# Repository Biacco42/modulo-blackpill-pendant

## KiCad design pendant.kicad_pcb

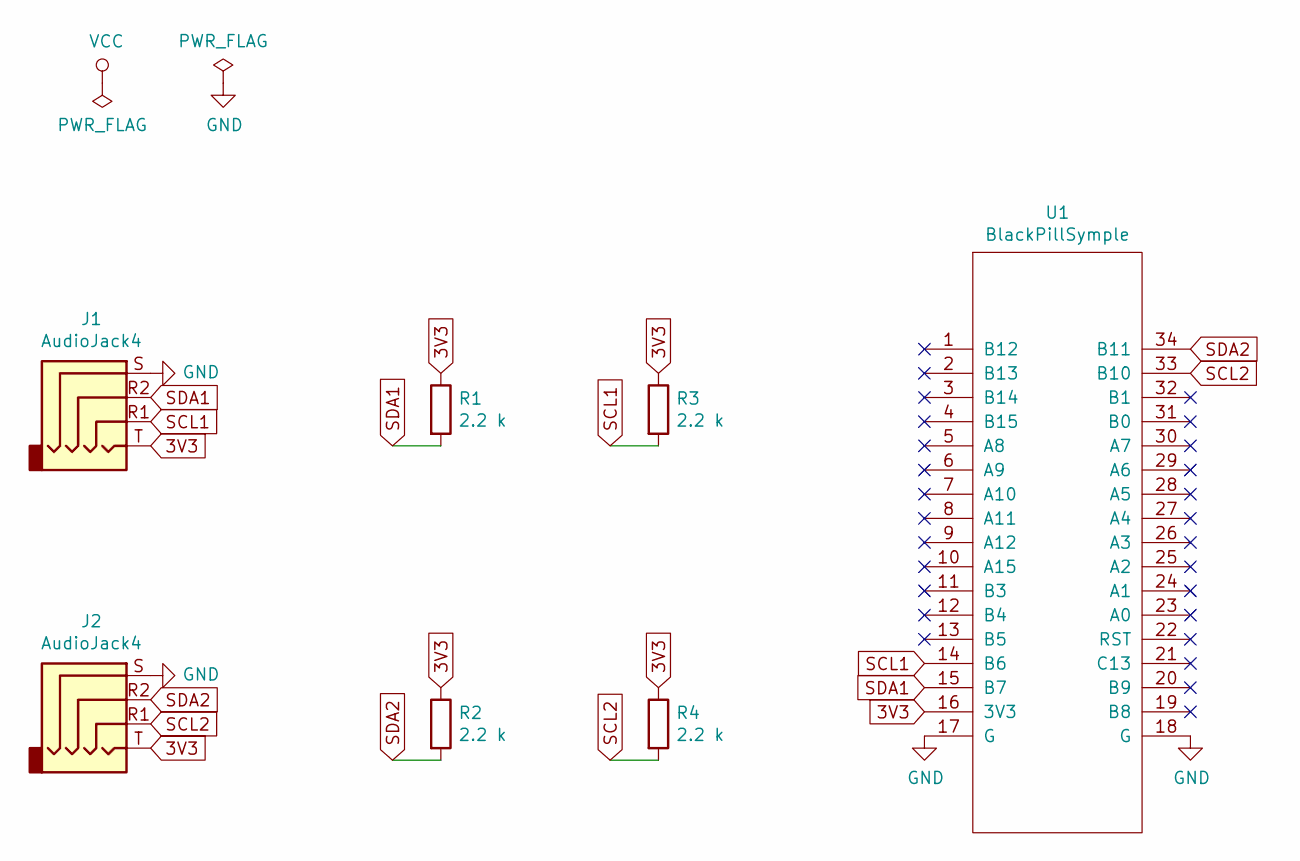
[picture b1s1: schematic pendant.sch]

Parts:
J1, J2: AudioJack4; TRRS_SMD_PJ320
R1, R2, R3, R4: 2.2 k; R_0603_1608Metric
U1: BlackPillSymple; BlackPillSimple

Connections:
3V3: J1.T, J2.T, R1.1, R2.1, R3.1, R4.1, U1.16 (3V3)
GND: J1.S, J2.S, U1.17 (G), U1.18 (G)
SCL1: J1.R1, R3.2, U1.14 (B6)
SCL2: J2.R1, R4.2, U1.33 (B10)
SDA1: J1.R2, R1.2, U1.15 (B7)
SDA2: J2.R2, R2.2, U1.34 (B11)

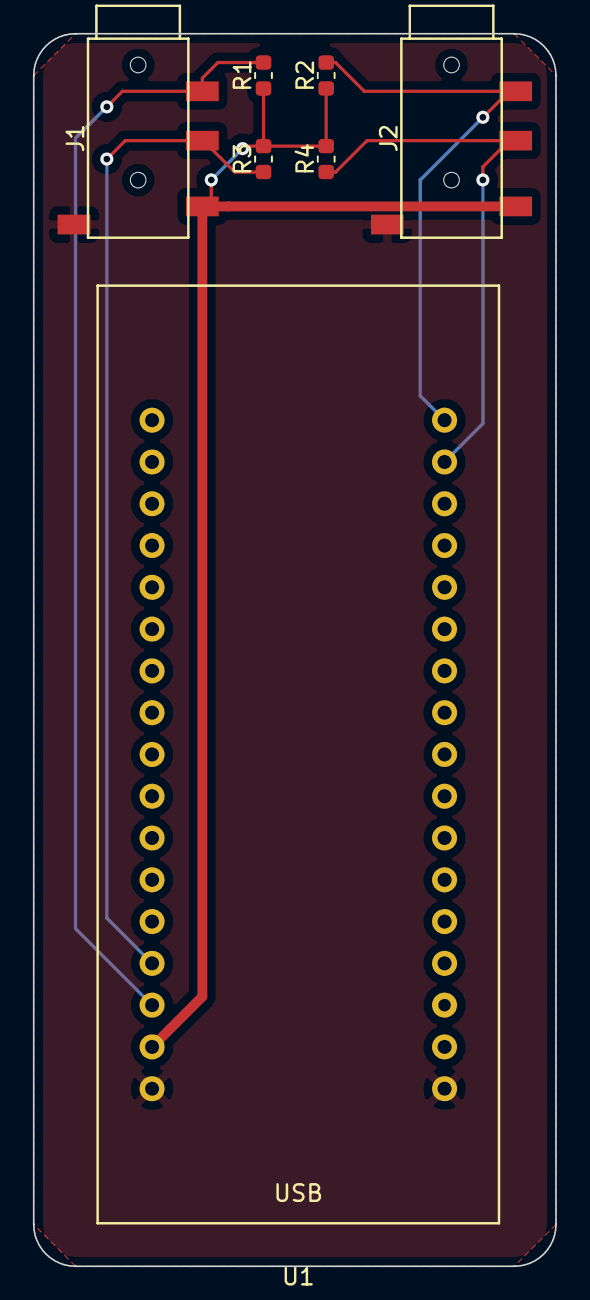
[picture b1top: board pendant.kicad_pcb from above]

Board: 2 copper layers, 31.8 x 74.9 mm, 7 parts (0 on the bottom side), 6 nets.

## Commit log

2018-09-24 Add library and bind footprint
2018-10-13 Clean up project
2018-10-13 Pendant 0.1.0
2018-10-13 Plot gerber
2018-10-28 Plot gerber for production
2018-12-16 Update schematics for beta
2018-12-16 Updaet PCB design
2018-12-16 Fix power line width
